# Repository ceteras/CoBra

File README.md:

# CoBra

CoBra is a Z80 computer designed in 1986 at ITCI, a research center in Brasov, Romania.  

In its official version, its specs are:
- 3.5MHz Z80A CPU
- 64KB ram, made up of 4 banks of 8x 4116 chips each
- 2KB - 16KB ROM boot code (original firmware fits in 2K)
- 16KB ROM for the BASIC interpreter (8x 2716 or 4x 2732)
- 256 x 192 resolution ZX Spectrum video interface
- 58 keys keyboard, featuring 50 keys for ZX Spectrum mode plus 8 for CP/M
- i8272 floppy interface - on a daughter board (not included in the repo for now)
- RS232 port (bit-banged)
- joystick port
- 8 bit parallel port, input only, signals shared with the joystick interface
- extension port using a 3x32 pin DIN41612 connector

It's a two-in-one machine, it can be either a ZX Spectrum compatible or a CP/M machine.  
CoBra has three different memory maps: one for power-on, one for ZX Spectrum, and one for CP/M.  
The memory configuration change is done in software, using the bit 7 of the R register.  

On power-on, the memory map includes both ROMs, and RAM banks 0 and 1.  
Cobra boots from the small 2K ROM, it can display on the screen and copy code to RAM.  
Code can be copied from ROM for ZX Spectrum mode, and from the floppy interface for CP/M.  
Tape interface can also be an option, which should be great for development.  

After copying the code, it will switch the memory map to te desired architecture.  
ROMs are disabled now and execution continues from the 64KB of RAM.  

Many thanks to [cobrasov.com](https://cobrasov.com/CoBra%20Project/index.html), my main inspiration source in this endeavour.  
You can find out a lot about this incredible machine on the website, including many improvements made to the original boards by the community.  
Gerber files are also available there for these improved versions, all tested and working great!  

This repo is a "revival" approach, aiming to re-create the original computer in Kicad, adding only some minor tweaks.  
Current status: 
- the board is built (see bottom image), there were some pain points I should document here
- a floppy interface was also built, works with a modified BASIC (gerbers are Ver.1.2 on "Floppy" IF section on [cobrasov.com](https://cobrasov.com/CoBra%20Project/index.html).
- CP/M not possible to test yet, all versions I can get access to need a 80KB RAM upgrade.

Links:
- [2 Layer PCB project](https://github.com/ceteras/CoBra/tree/main/mainboard/2layer) - a 4 layer version is in the works too
- [Schematic in pdf format](https://github.com/ceteras/CoBra/blob/main/main.pdf)
- [Gerber files](https://github.com/ceteras/CoBra/tree/main/mainboard/2layer/kicad/fabrication)
- [Interactive BOM](https://github.com/ceteras/CoBra/blob/main/mainboard/2layer/kicad/bom/ibom.html)
- [A PAL encoder with S-Video connector](https://github.com/ceteras/CoBra/tree/main/s-video) - a draft, not tested yet
- [An USB keyboard adapter](https://github.com/ceteras/CoBra/tree/main/adapter/USB%20Keyboard) - this one is also not final, an experiment

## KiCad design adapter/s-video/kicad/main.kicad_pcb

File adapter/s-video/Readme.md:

# S-Video Adapter for CoBra

Work in progress, untested.

This board is intended to connect to CoBra's video connector (J1).
It converts RGBI to PAL S-Video signals.

The schematic is inspired by [DonSuperfo's](https://github.com/DonSuperfo) [Superfo-Harlequin-128](https://github.com/DonSuperfo/Superfo-Harlequin-128).

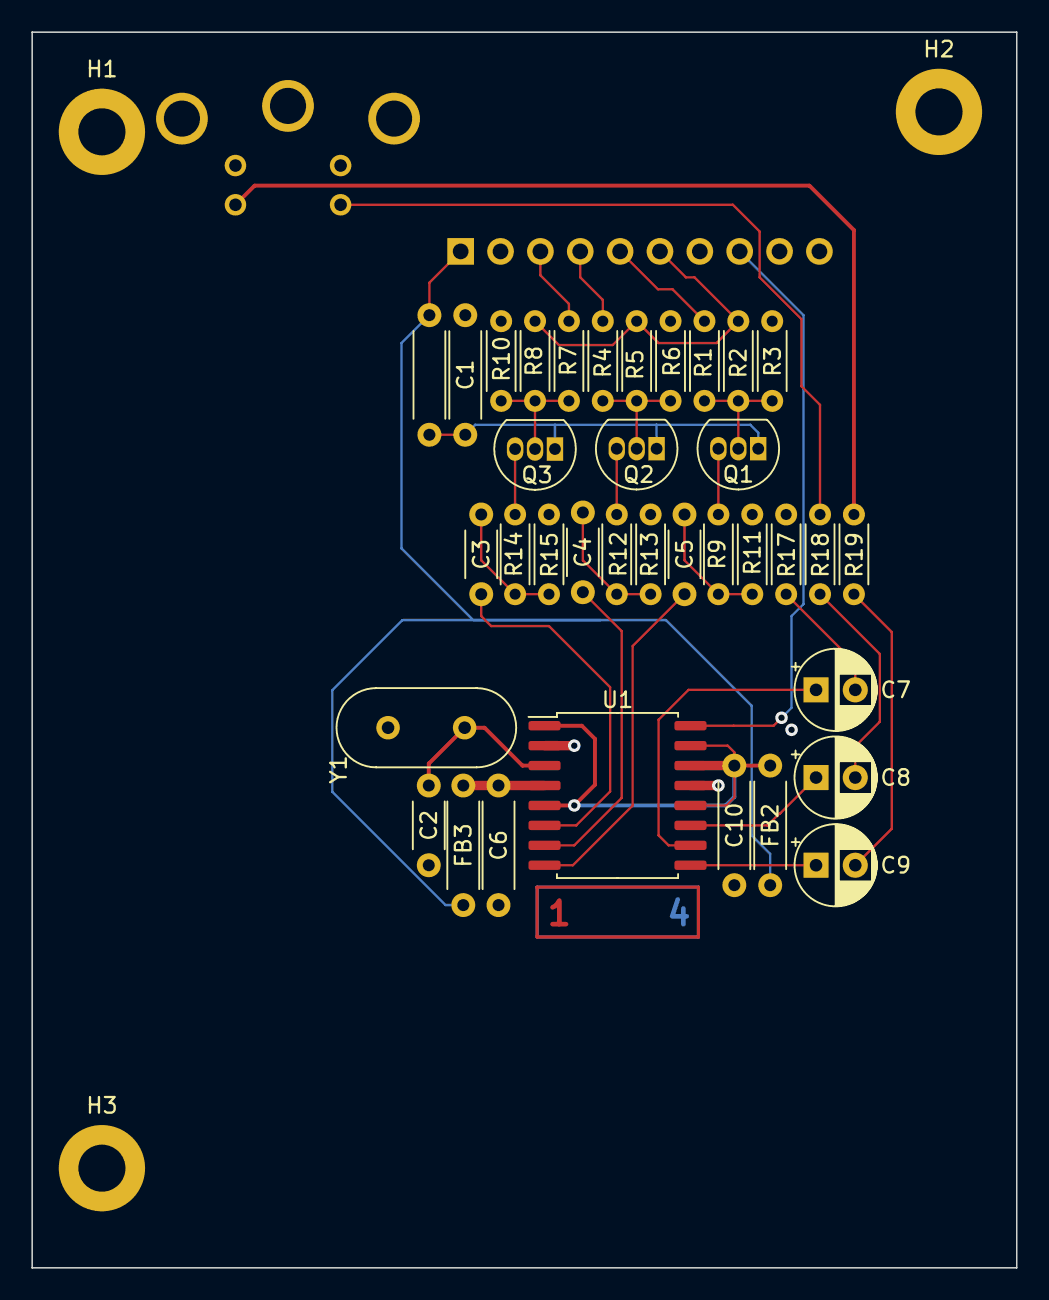
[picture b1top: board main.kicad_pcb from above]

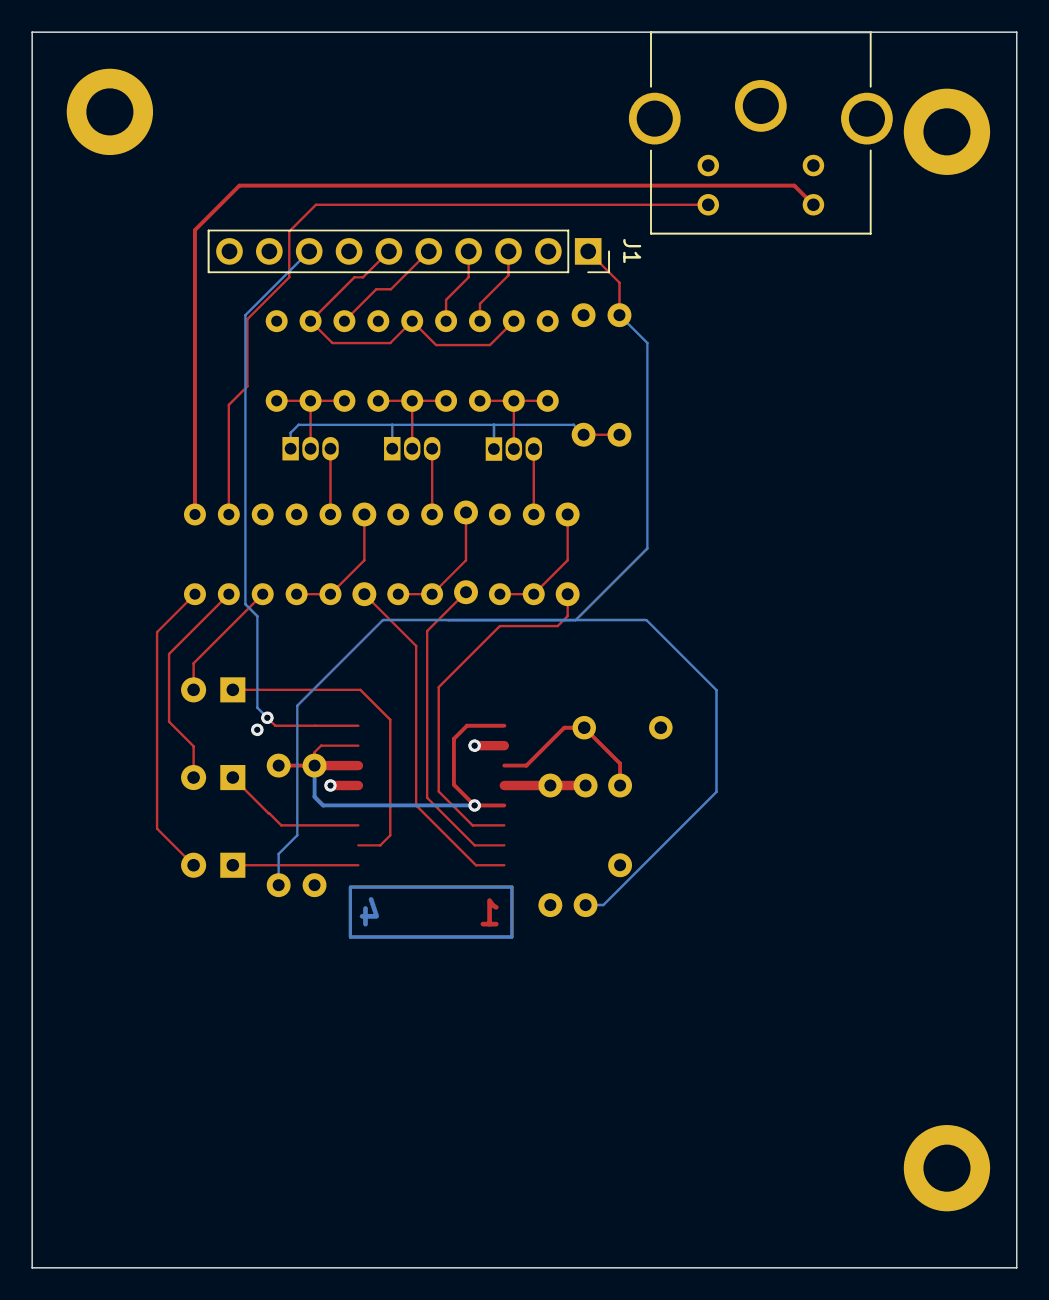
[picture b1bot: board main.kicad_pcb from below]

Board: 4 copper layers, 62.7 x 78.7 mm, 41 parts (2 on the bottom side), 31 nets.

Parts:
C1, C6, C10: 100n; C_THT_762_254
C2: 10p; C_THT_508_254
C3, C4, C5: 100n; C_THT_508_254
C7, C8, C9: 100u; CP_Radial_D5.0mm_P2.50mm
FB1, FB2, FB3: FerriteBead_Small; C_THT_762_254
H1, H2, H3: MountingHole_Pad; MountingHole_3mm_Pad
J1: Conn_01x10; PinSocket_1x10_P2.54mm_Vertical
J2: Mini-DIN-4; S-Video
Q1, Q2, Q3: BC548; TO-92_Inline
R1, R4, R7: 3K9; R_Axial_DIN0204_L3.6mm_D1.6mm_P5.08mm_Horizontal
R2, R5, R8: 18K; R_Axial_DIN0204_L3.6mm_D1.6mm_P5.08mm_Horizontal
R3, R6, R10: 2K2; R_Axial_DIN0204_L3.6mm_D1.6mm_P5.08mm_Horizontal
R9, R12, R14: 68; R_Axial_DIN0204_L3.6mm_D1.6mm_P5.08mm_Horizontal
R11, R13, R15, R17, R18, R19: 75; R_Axial_DIN0204_L3.6mm_D1.6mm_P5.08mm_Horizontal
U1: SOIC-16W_7.5x10.3mm_P1.27mm
Y1: 17.73448; Crystal_HC49-4H_Vertical

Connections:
/APOS: C6.1, FB3.1, U1.4 (APOS)
/B: J1.5, R1.2
/BIN: C5.1, R9.2, R11.1
/CRMA: J2.4, R19.2
/DPOS: C10.1, FB2.1, U1.1 (STND), U1.5 (ENCD), U1.12 (SELECT), U1.14 (DPOS), U1.15 (VSYNC)
/G: J1.4, R4.2
/GIN: C4.1, R12.2, R13.1
/I: J1.6, R2.2, R5.2, R8.2
/LUMA: J2.3, R18.2
/R: J1.3, R7.2
/RIN: C3.1, R14.2, R15.1
/SYNC: J1.8, U1.16 (HSYNC)
GNDD: C1.2, C2.1, C6.2, C10.2, H1.1, H2.1, H3.1, J1.2, J1.10, J2.1, J2.2, R3.1, R6.1, R10.1, R11.2, R13.2, R15.2, U1.2 (AGND), U1.13 (DGND), Y1.2
unnamed: C7.2, R17.1
unnamed: C8.2, R18.1
unnamed: C9.2, R19.1
unnamed: Q1.2 (B), R1.1, R2.1, R3.2
unnamed: C1.1, FB1.1, Q1.1 (C), Q2.1 (C), Q3.1 (C)
unnamed: Q1.3 (E), R9.1
unnamed: Q2.2 (B), R4.1, R5.1, R6.2
unnamed: Q2.3 (E), R12.1
unnamed: Q3.2 (B), R7.1, R8.1, R10.2
unnamed: Q3.3 (E), R14.1
unnamed: C5.2, U1.8 (BIN)
unnamed: C7.1, U1.10 (CMPS)
unnamed: C9.1, U1.9 (CRMA)
unnamed: C2.2, U1.3 (FIN), Y1.1
unnamed: C4.2, U1.7 (GIN)
unnamed: C8.1, U1.11 (LUMA)
unnamed: C3.2, U1.6 (RIN)
VCC: FB1.2, FB2.2, FB3.2, J1.1

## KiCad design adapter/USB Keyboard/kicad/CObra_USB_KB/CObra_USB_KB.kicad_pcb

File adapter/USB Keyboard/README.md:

# USB Keyboard Adapter (experimental)

Based on RP2040 Zero, emulates the CoBra switch matrix keyboard. 

The USB keyboard is connected to RP2040 USB port. Key codes are decoded and translated to an 8 byte array.
RP2040 reads the matrix column bus (KC[8..15] connected to A[8..15] through diodes) and sends the data  
corresponding to each key pressedi, from the array to the KR[0..5] bus.

Inputs to RP2040 are pulled high to 3.3V, so in theory this should be safe, as the 5V A[8..15] bus is behind reverse  
polarized diodes.  
Outputs are pulled high to 5V on the CoBra mainboard, hence the schottky diodes, for protection.
The keyboard input is an 8255 and its input voltage thresholds are safe for 3.3V logic (minimum 2V for input "1").

Key mapping:
- ALT / ALT gr - Symbol Shift
- GUI (Win key) - Caps Shift
- Cursor keys - CS + 5,6,7,8
- Backspace - CS + 0
- Insert - CS + 1 (edit)
- Application menu key - SS + X (pound)
- all symbols on a US keyboard [{]};:'"\|,<.>/?!@#$%^&*()_-+=   
  are mapped to their coreesponding CoBra key combinations  
  eg ")" - SS + 9, "~" - Extended mode + SS + A

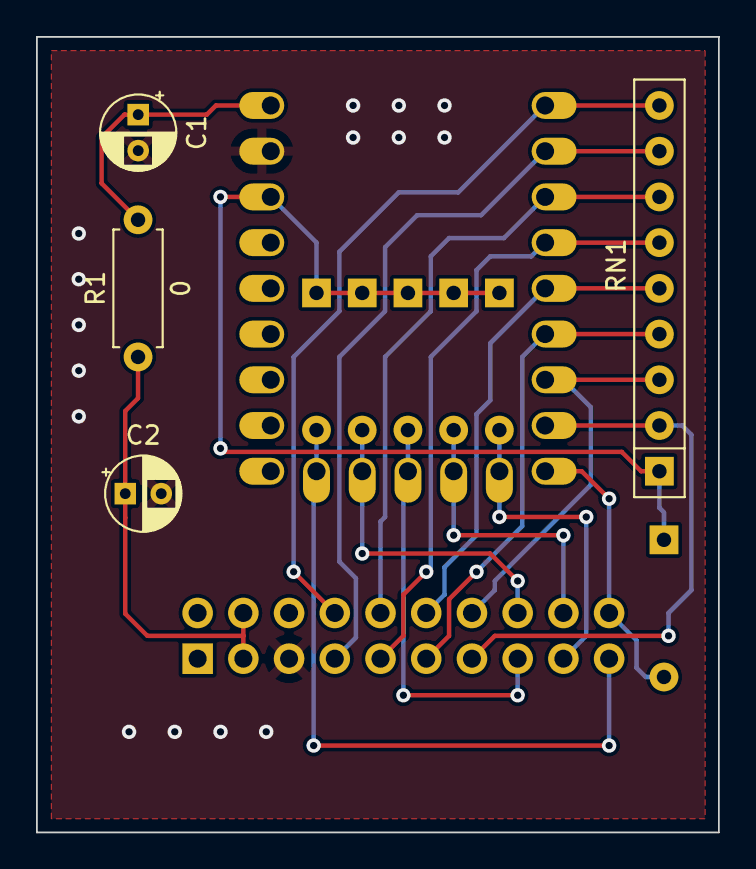
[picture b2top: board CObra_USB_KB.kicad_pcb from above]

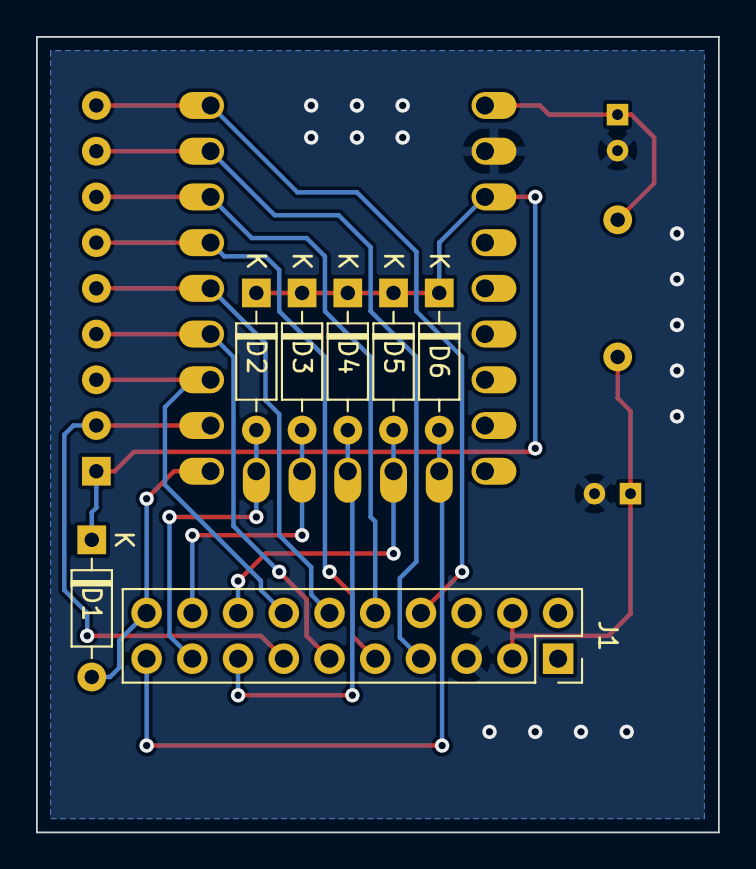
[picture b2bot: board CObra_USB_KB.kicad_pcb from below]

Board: 2 copper layers, 37.9 x 44.2 mm, 12 parts (7 on the bottom side), 18 nets.

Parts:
C1, C2: 10u; CP_Radial_D4.0mm_P2.00mm
D1, D2, D3, D4, D5, D6: 1N5711; D_DO-35_SOD27_P7.62mm_Horizontal
J1: Conn_02x10_Odd_Even; PinSocket_2x10_P2.54mm_Vertical
R1: 0; R_Axial_DIN0207_L6.3mm_D2.5mm_P7.62mm_Horizontal
RN1: 8x4K7; R_Array_SIP9
U1: rp2040-zero; rp2040-zero-tht

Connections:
/KC8: J1.8, RN1.9 (R8), U1.1 (0)
/KC9: J1.7, RN1.8 (R7), U1.2 (1)
/KC10: J1.10, RN1.7 (R6), U1.3 (2)
/KC11: J1.9, RN1.6 (R5), U1.4 (3)
/KC12: J1.12, RN1.5 (R4), U1.5 (4)
/KC13: J1.11, RN1.4 (R3), U1.6 (5)
/KC14: J1.14, RN1.3 (R2), U1.7 (6)
/KC15: J1.13, RN1.2 (R1), U1.8 (7)
/KR0: D1.2 (A), J1.20, U1.9 (8)
/KR1: D2.2 (A), J1.17, U1.10 (9)
/KR2: D3.2 (A), J1.18, U1.11 (10)
/KR3: D4.2 (A), J1.15, U1.12 (11)
/KR4: D5.2 (A), J1.16, U1.13 (12)
/KR5: D6.2 (A), J1.19, U1.14 (13)
/V3_3: D1.1 (K), D2.1 (K), D3.1 (K), D4.1 (K), D5.1 (K), D6.1 (K), RN1.1 (common), U1.21 (3V3)
GNDD: C1.2, C2.2, J1.5, U1.22 (GND)
unnamed: C1.1, R1.2, U1.23 (5V)
VCC: C2.1, J1.3, J1.4, R1.1

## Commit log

2023-11-14 Initial schematic pdf
2023-11-15 Initial commit of the original 2 layers Kicad project
2023-11-15 Changed floppy connector, fixed some library paths
2023-11-15 Fixed some libraries
2023-11-15 Update schematic pdf
2023-11-15 Another update to schematic pdf
2023-11-15 Fix resistor values on video memory page
2023-11-16 add mainboard image
2023-11-16 prototype board photo
2023-11-16 cleanup
2023-11-16 gitignore, cleanup
2023-11-16 Fixed some resistor values
2023-11-16 Fixes for PCB DRC: trace clearance, footprints, board edges
2023-11-16 modified footprint files
2023-11-17 Added 3D symbol for DIN-5, plus some silskreen cleanup
2023-11-17 resize main.png
2023-11-17 Changed images
2023-11-17 Images again
2023-11-17 More fixes after running DRC. Silskcreen overlaps, other warnings
2023-11-17 new pics
2023-11-17 Fabrication outputs: gerber, drill, bom added
2023-11-18 s-video board
2023-11-21 s-video readme
2023-11-24 small change in README
2023-11-27 Interactive BOM file added
2023-11-28 Some clarifications in README
2023-11-28 README
2023-11-28 another README rephrasing
2023-11-28 README typos
2023-11-29 removed mounting holes and H1,H3 placeholders from the BOM/ibom, align C25 on PCB
2023-12-20 update U14 symbol name to 74LS10
2023-12-21 changed mounting holes to 3mm, new gerbers
2024-01-12 Update README.md
    New image, project status update.
2024-01-12 some cleanup
2024-05-01 RP2040 Zero based USB Keyboard adapter
2024-06-24 Changes to folder structure
2024-06-24 renamed old uf2 file
2024-06-24 usb adapter source files
2024-06-24 Removed Readme file, will add one when ready
2024-06-28 removed backups files
2024-06-28 update to latest changes in mainboard schematic
2024-06-28 usb keyboard adapter schematic
2024-06-28 add latest uf2 file
2024-06-29 cleanup, readme updates
2024-06-30 case folder
2024-06-30 case readme change
2024-06-30 case readme changes
2024-06-30 moved folders around
2024-06-30 fix svideo readme
2024-09-22 New pcb photo
2024-09-22 small updates
2025-03-16 fixes for usb keyboad adapter
